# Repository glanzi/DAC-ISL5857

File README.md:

# DAC ISL5857

The Pmod compatible DAC board is based on the Intersil ISL5857 chip.

## License
The DAC project is an open source project licensed under CERN Open Hardware Licence v1.2. Please see the included LICENSE file for details. If you do wish to distribute boards derived from this open source hardware project then you must also release the source files for the boards under CERN Open Hardware Licence v1.2. You are free to do this, but please improve upon the original design and provide a tangible benefit for users of the board.

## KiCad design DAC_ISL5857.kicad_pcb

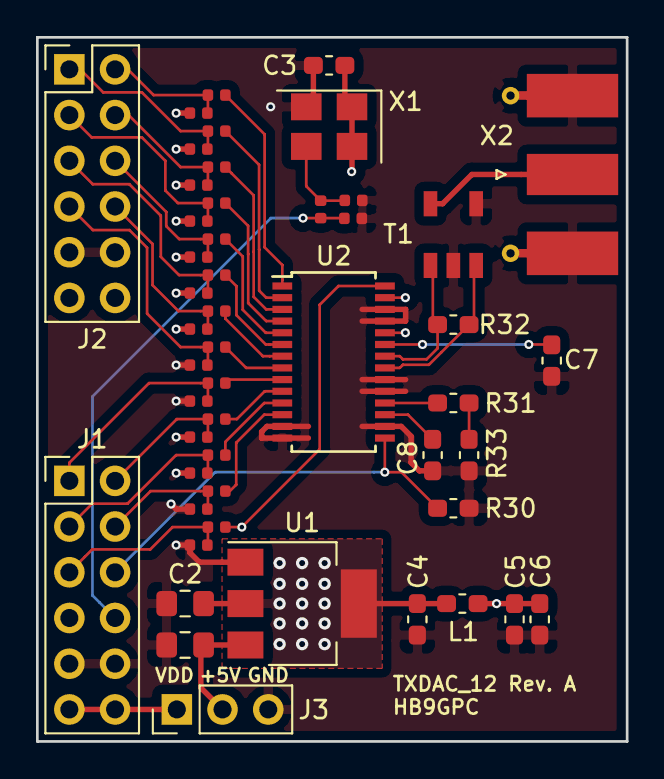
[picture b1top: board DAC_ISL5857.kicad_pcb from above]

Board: 4 copper layers, 32.8 x 39.1 mm, 50 parts (0 on the bottom side), 41 nets.

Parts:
C1, C2: 10uF; C_0805_2012Metric_Pad1.15x1.40mm_HandSolder
C3, C4, C5, C7, C8: 0.1uF; C_0603_1608Metric_Pad1.05x0.95mm_HandSolder
C6: 10uF; C_0603_1608Metric_Pad1.05x0.95mm_HandSolder
J1: P102; PinHeader_2x06_P2.54mm_Vertical
J2: P101; PinHeader_2x06_P2.54mm_Vertical
J3: P103; PinHeader_1x03_P2.54mm_Vertical
L1: 10uH; L_0603_1608Metric_Pad1.05x0.95mm_HandSolder
R1, R2, R3, R4, R5, R6, R7, R8, R9, R10, R11, R12, R13, R14, R29: 100; R_0402_1005Metric
R15: 0; R_0402_1005Metric
R16, R17, R18, R19, R20, R21, R22, R23, R24, R25, R26, R27, R28: 22; R_0402_1005Metric
R30: 0; R_0603_1608Metric_Pad1.05x0.95mm_HandSolder
R31: 1.8K; R_0603_1608Metric_Pad1.05x0.95mm_HandSolder
R32: 49.9; R_0603_1608Metric_Pad1.05x0.95mm_HandSolder
R33: 120; R_0603_1608Metric_Pad1.05x0.95mm_HandSolder
T1: 1:1; MABAES0060
U1: LD1117S33CTR; SOT-223-3_TabPin2
U2: ISL5857; TSSOP-28_4.4x9.7mm_P0.65mm
X1: ASFL1; Crystal_SMD_Abracon_ASFL1-4pin_5.0x3.2mm
X2: ANT; SMA_Molex_73251-1153_EdgeMount_Horizontal

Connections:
+3.3VADC: C5.2, C6.2, L1.1, U2.24
+3V3: C2.2, C3.2, C4.2, L1.2, U1.2, U2.27, X1.1, X1.4
+5V: C1.2, J3.2, U1.3
/CLK: J1.5, R1.2, R28.2
/D0: J1.4, R14.2, R27.2
/D1: J1.3, R12.2, R26.2
/D2: J1.2, R9.2, R25.2
/D3: J1.1, R7.2, R24.2
/D4: J2.7, R5.2, R23.2
/D5: J2.8, R3.2, R22.2
/D6: J2.5, R13.1, R21.2
/D7: J2.6, R11.1, R20.2
/D8: J2.3, R8.1, R19.2
/D9: J2.4, R6.1, R18.2
/D10: J2.1, R4.1, R17.2
/D11: J2.2, R2.1, R16.2
/PD: J1.6, R30.2, U2.15
/RF_N: R32.2, T1.1, U2.21
/RF_P: R32.1, T1.3, U2.22
GND: C1.1, C2.1, C3.1, C4.1, C5.1, C6.1, C7.1, C8.1, J1.9, J1.10, J2.9, J2.10, J3.3, R1.1, R2.2, R3.1, R4.2, R5.1, R6.2, R7.1, R8.2, R9.1, R10.1, R11.2, R12.1, R13.2, R14.1, R29.1, R30.1, R33.1, T1.2, T1.5, U1.1, U2.13, U2.14, U2.16, U2.19, U2.20, U2.25, U2.26, X1.2, X2.2
unnamed: C7.2, U2.23
unnamed: C8.2, U2.17
unnamed: R10.2, R15.2, X1.3
unnamed: R16.1, U2.1
unnamed: R17.1, U2.2
unnamed: R18.1, U2.3
unnamed: R19.1, U2.4
unnamed: R20.1, U2.5
unnamed: R21.1, U2.6
unnamed: R22.1, U2.7
unnamed: R23.1, U2.8
unnamed: R24.1, U2.9
unnamed: R25.1, U2.10
unnamed: R26.1, U2.11
unnamed: R27.1, U2.12
unnamed: R28.1, U2.28
unnamed: R31.1, R33.2
unnamed: R31.2, U2.18
unnamed: T1.4, X2.1
SYS_MCLK: J1.8, R15.1, R29.2
VDD: J1.11, J1.12, J3.1

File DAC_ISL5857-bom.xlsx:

Quantity | Reference | Value | Footprint | Manufacturer | MPN | Digikey
2 | C1 C2 | 10uF | Capacitor_SMD:C_0805_2012Metric_Pad1.15x1.40mm_HandSolder
1 | C6 | 10uF | Capacitor_SMD:C_0603_1608Metric_Pad1.05x0.95mm_HandSolder
5 | C3 C4 C5 C7 C8 | 0.1uF | Capacitor_SMD:C_0603_1608Metric_Pad1.05x0.95mm_HandSolder
1 | J1 | P102 | Connector_PinHeader_2.54mm:PinHeader_2x06_P2.54mm_Vertical
1 | J2 | P101 | Connector_PinHeader_2.54mm:PinHeader_2x06_P2.54mm_Vertical
1 | J3 | P103 | Connector_PinHeader_2.54mm:PinHeader_1x03_P2.54mm_Vertical
1 | L1 | 10uH | Inductor_SMD:L_0603_1608Metric_Pad1.05x0.95mm_HandSolder
15 | R1 R10 R11 R12 R13 R14 R2 R29 R3 R4 R5 R6 R7 R8 R9 | 100 | Resistor_SMD:R_0402_1005Metric
1 | R15 | 0 | Resistor_SMD:R_0402_1005Metric
13 | R16 R17 R18 R19 R20 R21 R22 R23 R24 R25 R26 R27 R28 | 22 | Resistor_SMD:R_0402_1005Metric
1 | R30 | 0 | Resistor_SMD:R_0603_1608Metric_Pad1.05x0.95mm_HandSolder
1 | R31 | 1.8K | Resistor_SMD:R_0603_1608Metric_Pad1.05x0.95mm_HandSolder
1 | R32 | 49.9 | Resistor_SMD:R_0603_1608Metric_Pad1.05x0.95mm_HandSolder
1 | R33 | 120 | Resistor_SMD:R_0603_1608Metric_Pad1.05x0.95mm_HandSolder
1 | T1 | 4.2361111111111106E-2 | dra818:MABAES0060 |  |  | 1465-1317-1-ND‎
1 | U1 | LD1117S33CTR | Package_TO_SOT_SMD:SOT-223-3_TabPin2 |  |  | 497-1241-1-ND‎
1 | U2 | ISL5857 | Package_SO:TSSOP-28_4.4x9.7mm_P0.65mm |  |  | ISL5857IAZ-ND‎
1 | X1 | ASFL1 | DRA818:Crystal_SMD_Abracon_ASFL1-4pin_5.0x3.2mm |  |  | 300-8269-1-ND‎
1 | X2 | ANT | Connector_Coaxial:SMA_Molex_73251-1153_EdgeMount_Horizontal
 | Green items may be substituted with parts that have identical or better specifi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
 | Red items may not be substituted with different part numbers

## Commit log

2018-11-21 Update PCB layout
2018-11-21 Generate Gerber files
2018-11-21 Add 3D PCB image
2018-11-21 Fix typo
2018-11-23 Replace IC reg linear and clock footprint
2018-11-24 Add BOM
